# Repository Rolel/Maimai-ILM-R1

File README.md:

# Maimai LED - ILM-R1 remake

Remake of the ILM-R1 PCB used for lighting in Maimai arcade cabinet. This is not a 1:1 reproduction but a fully compatible and same light intensity as the original.

## BOM

* Inolux IN-P55TATRGB RGB leds (manufacturer ref: IN-P55TATRGB )
* 0805 resistors
  * Red: 450 ohms
  * Green: 130 ohms
  * Blue: 150 ohms
  
The resistors values have a some tolerance, even on original boards the value differs. 

## PCB

Kicad files are made with version 8. 

They can be produced at . Upload the `MaimaiLed.kicad_pcb.zip` file into the "Quick Order" tool, then keep default settings, that's all.

Even simpler, have a look at the .

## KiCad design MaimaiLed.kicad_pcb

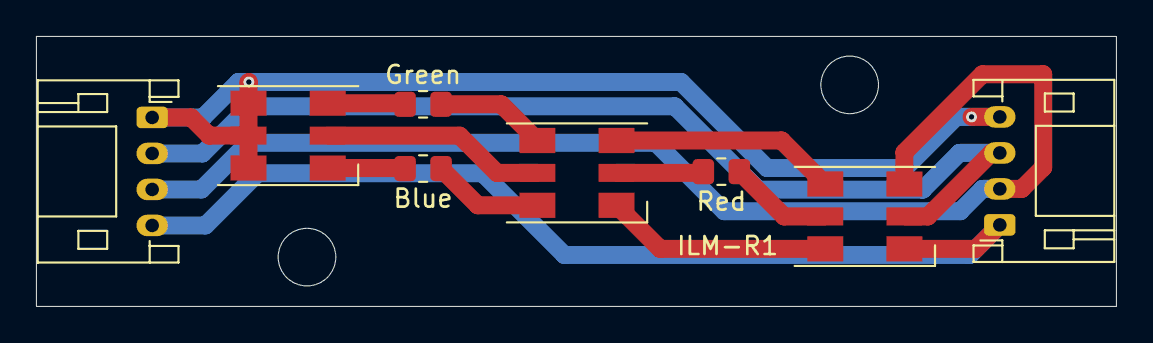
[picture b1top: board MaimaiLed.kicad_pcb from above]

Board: 2 copper layers, 60.0 x 15.0 mm, 10 parts (0 on the bottom side), 13 nets.

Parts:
Blue: 150; R_0805_2012Metric_Pad1.20x1.40mm_HandSolder
D1, D2, D3: Inolux_IN-P55TATRGB; LED_Inolux_IN-P55TATRGB_PLCC6_5.0x5.5mm_P1.8mm
Green: 130; R_0805_2012Metric_Pad1.20x1.40mm_HandSolder
H1, H2: MountingHole; MountingHole_3.2mm_M3
J1: ConnLeft; JST_PH_S4B-PH-K_1x04_P2.00mm_Horizontal
J2: ConnRightNP; JST_PH_S4B-PH-K_1x04_P2.00mm_Horizontal
Red: 450; R_0805_2012Metric_Pad1.20x1.40mm_HandSolder

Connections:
unnamed: D1.4 (AG), D1.5 (AR), D1.6 (AB), J1.1, J2.4
unnamed: Blue.2, D1.1 (KB)
unnamed: D1.3 (KG), Green.1
unnamed: D1.2 (KR), D2.5 (AR)
unnamed: Blue.1, D2.6 (AB)
unnamed: D2.4 (AG), Green.2
unnamed: D2.1 (KB), D3.6 (AB)
unnamed: D2.3 (KG), D3.4 (AG)
unnamed: D2.2 (KR), Red.2
unnamed: D3.5 (AR), Red.1
unnamed: D3.1 (KB), J1.4, J2.1
unnamed: D3.3 (KG), J1.3, J2.2
unnamed: D3.2 (KR), J1.2, J2.3

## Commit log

2024-09-21 Add Readme
2024-09-21 Add Kicad files
2024-09-21 Readme
2024-10-05 Updated Readme and project schematic
